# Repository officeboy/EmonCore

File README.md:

# EmonCore
Open Energy Monitor - All in One for the Spark Core/Photon

Based on work done in the [emonBase/NanodeRF](http://openenergymonitor.org/emon/emonBase/NanodeRF) project, Cinezaster porting [EmonLib](https://github.com/Cinezaster/EmonLib), and Nils Mattisson's [HttpClient](https://github.com/nmattisson/HttpClient) Library

This project aims in the same single unit direction as emonPi but sticks with arduino type programing and aims for a smaller form factor. 

Currently there is no support for RFM12B or RFM69CW devices.  

### Features

- Built in WiFi
- 8 12-bit Analog Channels
- 73Mhz ARM Cortex M3
- Flash via Web

## Guide

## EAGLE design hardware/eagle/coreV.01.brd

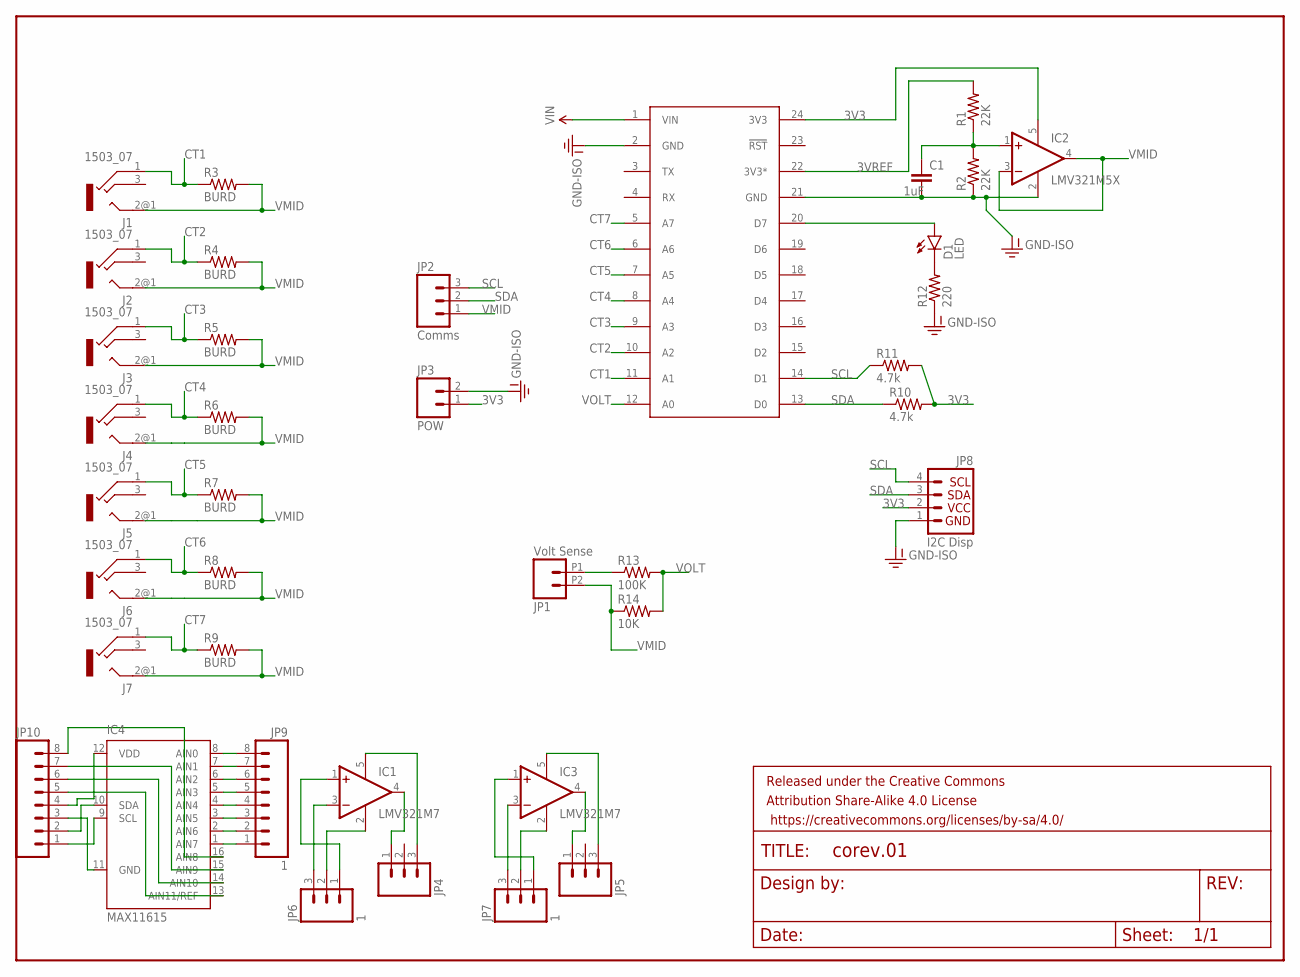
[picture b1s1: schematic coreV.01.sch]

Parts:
C1: 1uF; CAP-PTH-SMALL
D1: LED; LED3MM
FRAME1: emonCore; CREATIVE_COMMONS
IC1, IC3: LMV321M7; SC70-5L
IC2: LMV321M5X; SOT23-5
IC4: MAX11615; QSOP16
J1, J2, J3, J4, J5, J6, J7: 1503_07
JP1: Volt Sense; 1X02_2.54_SCREWTERM
JP2: Comms; 1X03
JP3: POW; 1X02
JP4, JP5: M03PTH; 1X03
JP6, JP7: 1; 1X03
JP8: I2C Disp; 1X04
JP9: 1; 1X08
JP10: M08SILK_FEMALE_PTH; 1X08
R1, R2: 22K; AXIAL-0.3
R3, R4, R5, R6, R7, R8, R9: BURD; AXIAL-0.3
R10, R11: 4.7k; AXIAL-0.3
R12: 220; AXIAL-0.3
R13: 100K; AXIAL-0.3
R14: 10K; AXIAL-0.3
U$1: SPARK_CORE

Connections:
3V3: IC2.5 (V+), JP3.1, JP8.2, R10.P$2 (2), R11.P$2 (2), U$1.24 (3V3)
3VREF: R1.P$2 (2), U$1.22 (3V3*)
CT1: J1.1, R3.P$1 (1), U$1.11 (A1)
CT2: J2.1, R4.P$1 (1), U$1.10 (A2)
CT3: J3.1, R5.P$1 (1), U$1.9 (A3)
CT4: J4.1, R6.P$1 (1), U$1.8 (A4)
CT5: J5.1, R7.P$1 (1), U$1.7 (A5)
CT6: J6.1, R8.P$1 (1), U$1.6 (A6)
CT7: J7.1, R9.P$1 (1), U$1.5 (A7)
GND-ISO: C1.2, IC2.2 (V-), JP3.2, JP8.1, R2.P$1 (1), R12.P$1 (1), U$1.2 (GND), U$1.21 (GND)
unnamed: D1.K (C), R12.P$2 (2)
unnamed: C1.1, IC2.1 (+IN), R1.P$1 (1), R2.P$2 (2)
unnamed: JP1.P1 (1), R13.P$1 (1)
unnamed: D1.A, U$1.20 (D7)
unnamed: IC3.2 (V-), JP7.2
unnamed: IC3.1 (+IN), JP7.1
unnamed: IC3.3 (-IN), JP7.3
unnamed: IC3.4 (OUT), JP5.1
unnamed: IC1.2 (V-), JP6.2
unnamed: IC3.5 (V+), JP5.3
unnamed: IC1.3 (-IN), JP6.3
unnamed: IC1.1 (+IN), JP6.1
unnamed: IC1.4 (OUT), JP4.1
unnamed: IC1.5 (V+), JP4.3
unnamed: IC4.1 (AIN7), JP9.1
unnamed: IC4.2 (AIN6), JP9.2
unnamed: IC4.3 (AIN5), JP9.3
unnamed: IC4.4 (AIN4), JP9.4
unnamed: IC4.5 (AIN3), JP9.5
unnamed: IC4.6 (AIN2), JP9.6
unnamed: IC4.7 (AIN1), JP9.7
unnamed: IC4.8 (AIN0), JP9.8
unnamed: IC4.9 (SCL), JP10.1
unnamed: IC4.10 (SDA), JP10.2
unnamed: IC4.11 (GND), JP10.3
unnamed: IC4.12 (VDD), JP10.4
unnamed: IC4.13 (AIN11/REF), JP10.5
unnamed: IC4.14 (AIN10), JP10.6
unnamed: IC4.15 (AIN9), JP10.7
unnamed: IC4.16 (AIN8), JP10.8
SCL: JP2.3, JP8.4, R11.P$1 (1), U$1.14 (D1)
SDA: JP2.2, JP8.3, R10.P$1 (1), U$1.13 (D0)
VIN: U$1.1 (VIN)
VMID: IC2.3 (-IN), IC2.4 (OUT), J1.2@1 (2), J2.2@1 (2), J3.2@1 (2), J4.2@1 (2), J5.2@1 (2), J6.2@1 (2), J7.2@1 (2), JP1.P2 (2), JP2.1, R3.P$2 (2), R4.P$2 (2), R5.P$2 (2), R6.P$2 (2), R7.P$2 (2), R8.P$2 (2), R9.P$2 (2), R14.P$1 (1)
VOLT: R13.P$2 (2), R14.P$2 (2), U$1.12 (A0)

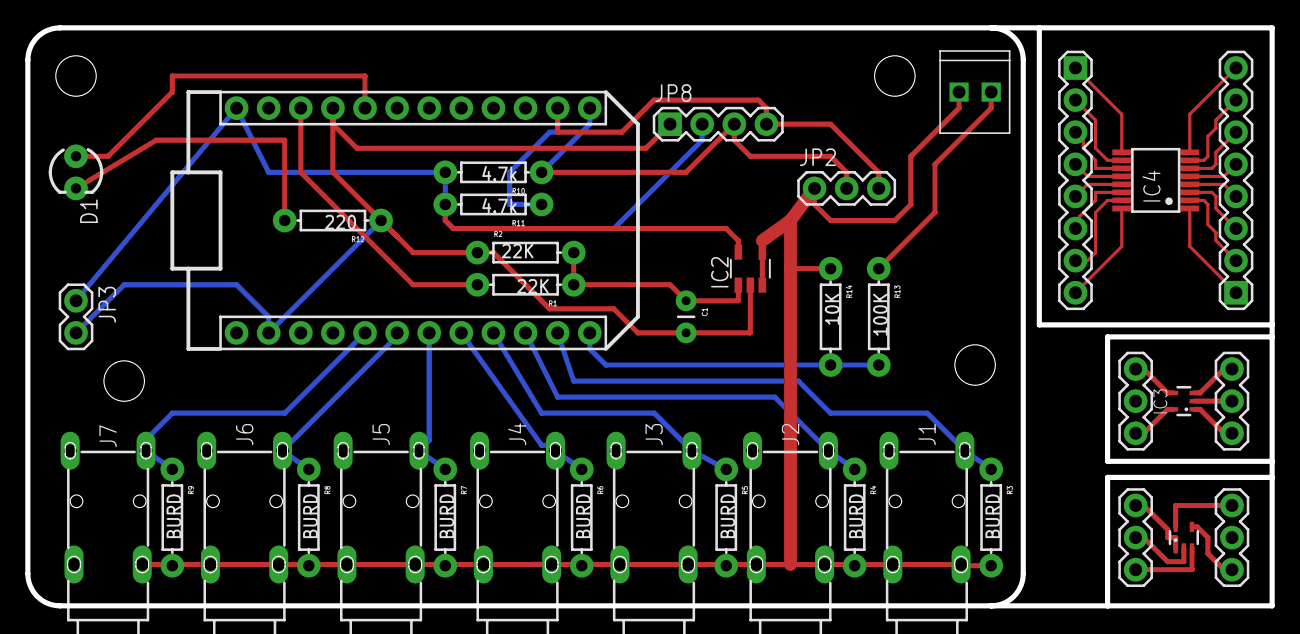
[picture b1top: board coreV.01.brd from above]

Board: 2 copper layers, 98.4 x 45.7 mm, 39 parts (0 on the bottom side), 44 nets.

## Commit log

2015-03-27 First Working
    Gets analog reading from A0 and A1
    Enables tinker so you can read and set values without sensor (does need
    some jumper wires since you can't write and read from the same pin)
2015-03-28 Added D7 blink on send and Vcal variable
2015-03-31 Start of rebase on emontx3 from nanodeRF
2015-04-01 Revert "Start of rebase on emontx3 from nanodeRF"
    This reverts commit 08fe7cee7cd59ef0e31d750fc931684b249a59a1.
2015-04-01 Revert "Revert "Start of rebase on emontx3 from nanodeRF""
    This reverts commit 33eafbb75076938f1f11204168eaa1d54870827a.
2015-04-01 Revert "Revert "Revert "Start of rebase on emontx3 from nanodeRF"""
    This reverts commit 871d2c3ea81144d46abe9197237618a9d577d539.
2015-04-01 Undoing my poorly chosen work from yesterday.
    Yo Dog, I hear you like reverts...
    I don't know if I will get the hang of this.
2015-04-01 Possibly a Rebase on the emontx v3.4 code
    But I don't think I like the complexity for now.
2015-04-01 Send to web on its own
2015-04-02 Added extra CT variable, and wifi rssi
    rssi locking up unit, need to research.
2015-04-02 Giving props
2015-04-14 Board layout changes
    and turned some packages into pin-outs.
2015-04-14 pics
2015-04-14 Pics and DRC ok
2015-04-16 Shrank PCB and added header pins
    changed a few names too
2015-04-20 Eagle design files
    to many issues with getting a good footprint in fritzing.
2015-04-22 Added display library
2015-04-22 Left a few bugs in update_display
2015-04-23 Adding some temp variables
    updated some comments, and turned tinker back on
2015-09-16 added work files
    Hopefully these can be usefull

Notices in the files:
parts and their libraries:
SparkFun-Capacitors: Licensing: Creative Commons ShareAlike 4.0 International - https://creativecommons.org/licenses/by-sa/4.0
SparkFun-Aesthetics: Released under the Creative Commons Attribution Share-Alike 4.0 License
SparkFun-Aesthetics: https://creativecommons.org/licenses/by-sa/4.0
